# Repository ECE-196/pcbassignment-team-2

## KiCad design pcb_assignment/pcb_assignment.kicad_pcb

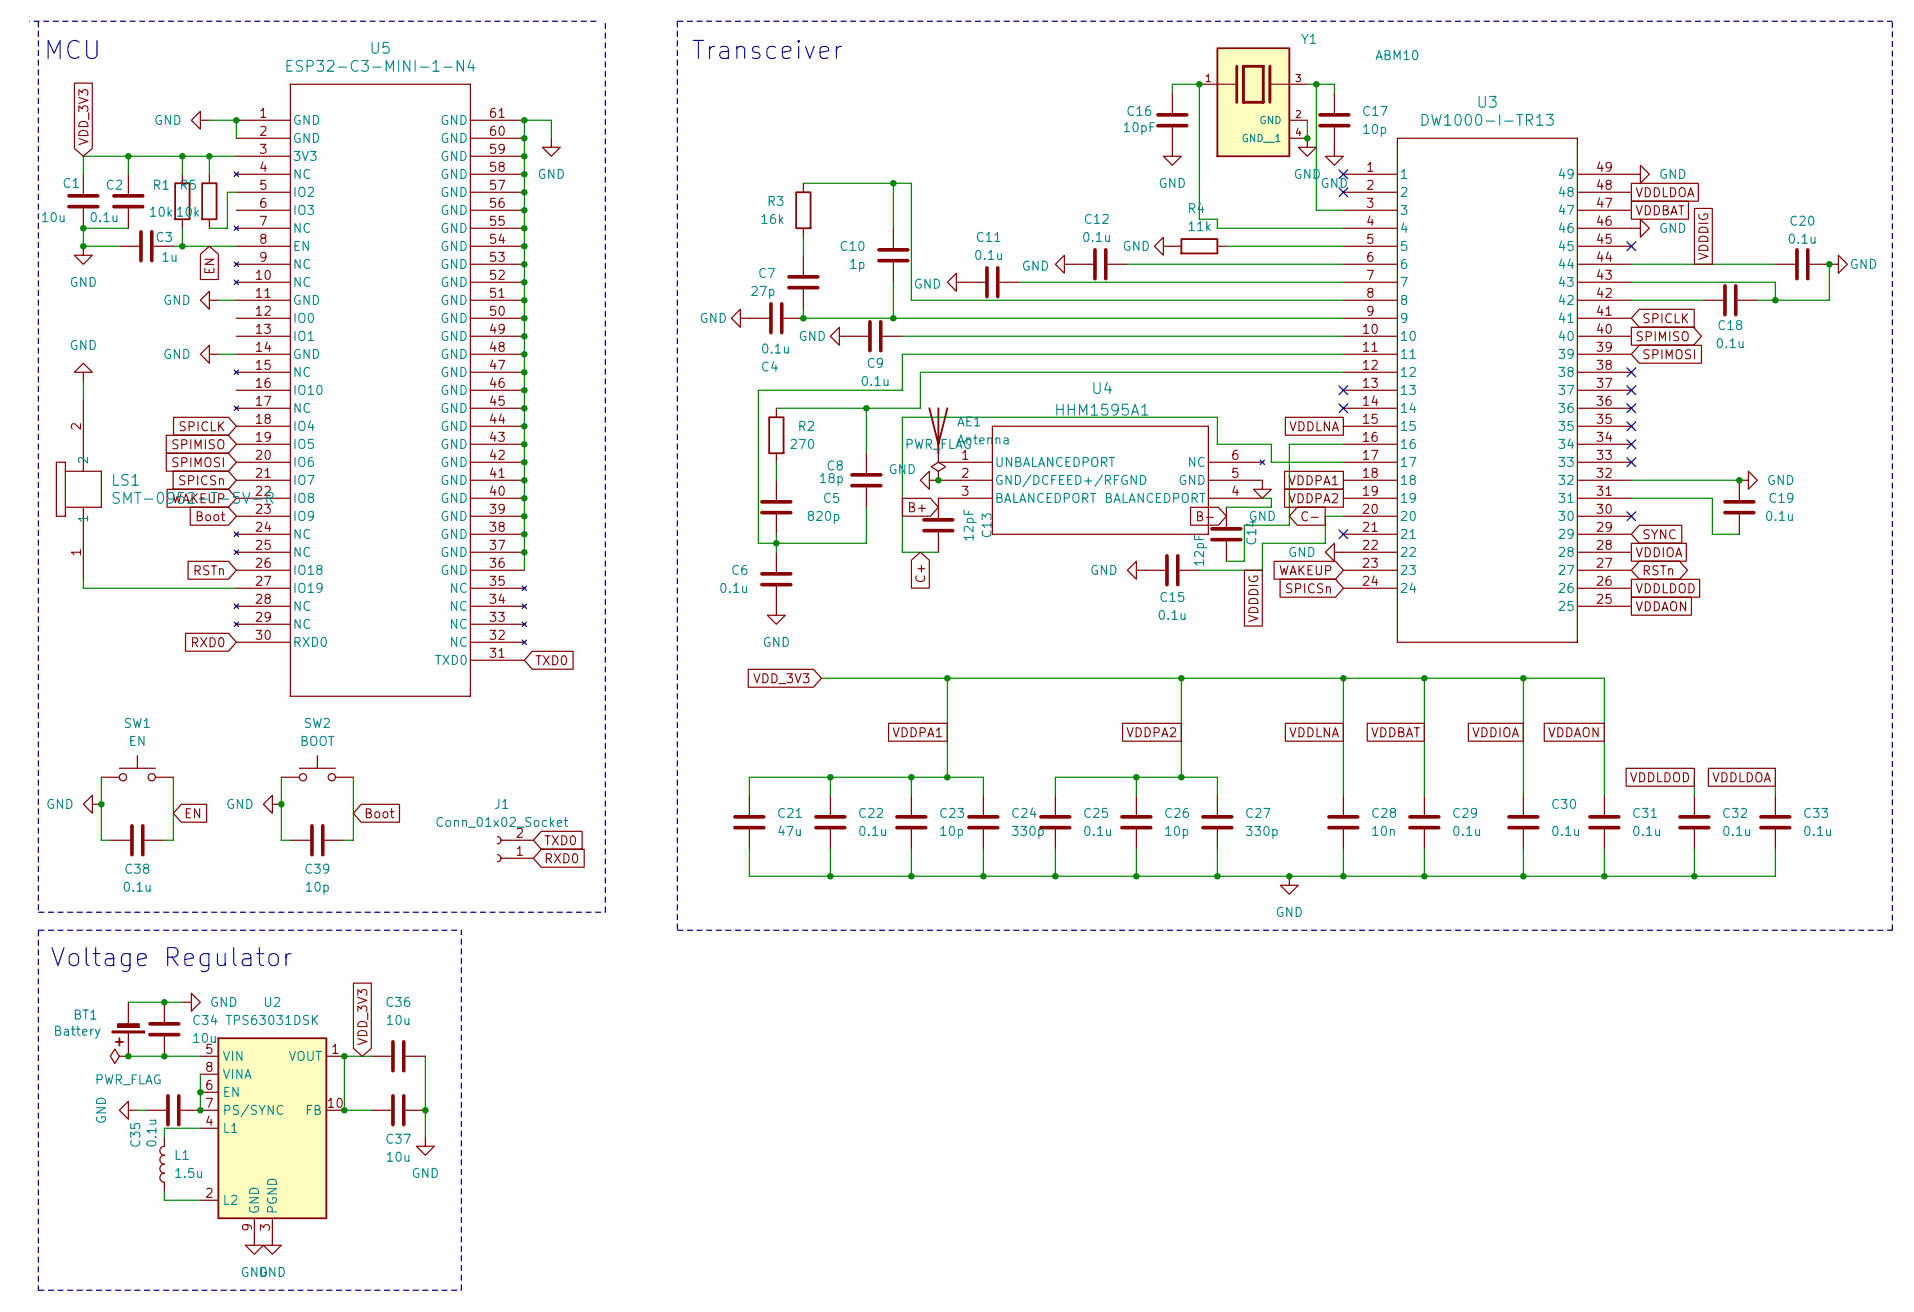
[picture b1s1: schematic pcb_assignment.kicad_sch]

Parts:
AE1: Antenna; AH086M_TAY
BT1: Battery; JST_ACH_BM02B-ACHSS-GAN-ETF_1x02-1MP_P1.20mm_Vertical
C1, C34, C36, C37: 10u; C_0402_1005Metric
C2, C4, C6, C9, C11, C12, C15, C18, C19, C20, C22, C25, C29, C30, C31, C32, C33, C35, C38: 0.1u; C_0402_1005Metric
C3: 1u; C_0402_1005Metric
C5: 820p; C_0402_1005Metric
C7: 27p; C_0402_1005Metric
C8: 18p; C_0402_1005Metric
C10: 1p; C_0402_1005Metric
C13, C14: 12pF; C_0402_1005Metric
C16: 10pF; C_0402_1005Metric
C17, C23, C26, C39: 10p; C_0402_1005Metric
C21: 47u; C_0402_1005Metric
C24, C27: 330p; C_0402_1005Metric
C28: 10n; C_0402_1005Metric
J1: Conn_01x02_Socket; PinHeader_1x02_P2.00mm_Horizontal
L1: 1.5u; L_Taiyo-Yuden_NR-30xx
LS1: SMT-0952-T-5V-R; SMT-0952-T-5V-R_PUI
R1, R5: 10k; R_0402_1005Metric
R2: 270; R_0402_1005Metric
R3: 16k; R_0402_1005Metric
R4: 11k; R_0402_1005Metric
SW1: EN; SW_PUSH_6mm
SW2: BOOT; SW_PUSH_6mm
U2: TPS63031DSK; WSON-10-1EP_2.5x2.5mm_P0.5mm_EP1.2x2mm
U3: DW1000-I-TR13; VFQFN48_12X12_QOR
U4: HHM1595A1; HHM-6_2P0X1P25
U5: ESP32-C3-MINI-1-N4; ESP32-C3-MINI-1_EXP
Y1: ABM10; XTAL_ABM10-165-38.400MHZ-T3; PARTREV 09.21.15

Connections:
Boot: C39.2, SW2.2, U5.23 (IO9)
C+: C13.2, U3.17
C-: C14.2, U3.16
EN: C3.2, C38.2, R1.2, SW1.2, U5.8 (EN)
GND: BT1.2 (-), C1.2, C2.2, C3.1, C4.2, C6.2, C9.2, C11.2, C12.2, C15.1, C16.2, C17.2, C18.2, C19.1, C20.2, C21.2, C22.2, C23.2, C24.2, C25.2, C26.2, C27.2, C28.2, C29.2, C30.2, C31.2, C32.2, C33.2, C34.1, C35.2, C36.2, C37.2, C38.1, C39.1, LS1.2, R4.2, SW1.1, SW2.1, U2.3 (PGND), U2.9 (GND), U2.11 (PGND), U3.22, U3.32, U3.43, U3.46, U3.49, U4.2 (GND/DCFEED+/RFGND), U4.5 (GND), U5.1 (GND), U5.2 (GND), U5.11 (GND), U5.14 (GND), U5.36 (GND), U5.37 (GND), U5.38 (GND), U5.39 (GND), U5.40 (GND), U5.41 (GND), U5.42 (GND), U5.43 (GND), U5.44 (GND), U5.45 (GND), U5.46 (GND), U5.47 (GND), U5.48 (GND), U5.49 (GND), U5.50 (GND), U5.51 (GND), U5.52 (GND), U5.53 (GND), U5.54 (GND), U5.55 (GND), U5.56 (GND), U5.57 (GND), U5.58 (GND), U5.59 (GND), U5.60 (GND), U5.61 (GND), Y1.2 (GND), Y1.4 (GND__1)
unnamed: AE1.1 (A), U4.1 (UNBALANCEDPORT)
unnamed: BT1.1 (+), C34.2, U2.5 (VIN)
unnamed: C5.1, R2.2
unnamed: C5.2, C6.1, C8.2, U3.11
unnamed: C7.1, R3.2
unnamed: C8.1, R2.1, U3.12
unnamed: C9.1, U3.10
unnamed: C10.1, R3.1, U3.8
unnamed: C4.1, C7.2, C10.2, U3.9
unnamed: C11.1, U3.7
unnamed: C12.1, U3.6
unnamed: C13.1, U4.3 (BALANCEDPORT)
unnamed: C14.1, U4.4 (BALANCEDPORT)
unnamed: C16.1, U3.4, Y1.1
unnamed: C17.1, U3.3, Y1.3
unnamed: C18.1, U3.42
unnamed: C19.2, U3.31
unnamed: R4.1, U3.5
unnamed: C35.1, U2.6 (EN), U2.7 (PS/SYNC), U2.8 (VINA)
unnamed: L1.2, U2.4 (L1)
unnamed: L1.1, U2.2 (L2)
unnamed: R5.2, U5.5 (IO2)
unnamed: LS1.1, U5.27 (IO19)
RSTn: U3.27, U5.26 (IO18)
RXD0: J1.1, U5.30 (RXD0)
SPICLK: U3.41, U5.18 (IO4)
SPICSn: U3.24, U5.21 (IO7)
SPIMISO: U3.40, U5.19 (IO5)
SPIMOSI: U3.39, U5.20 (IO6)
SYNC: U3.29
TXD0: J1.2, U5.31 (TXD0)
VDDAON: C1.1, C2.1, C21.1, C22.1, C23.1, C24.1, C25.1, C26.1, C27.1, C28.1, C29.1, C30.1, C31.1, C36.1, C37.1, R1.1, R5.1, U2.1 (VOUT), U2.10 (FB), U3.15, U3.18, U3.19, U3.25, U3.28, U3.47, U5.3 (3V3)
VDDDIG: C15.2, C20.1, U3.20, U3.44
VDDLDOA: C33.1, U3.48
VDDLDOD: C32.1, U3.26
WAKEUP: U3.23, U5.22 (IO8)

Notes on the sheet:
Voltage Regulator
MCU
Transceiver

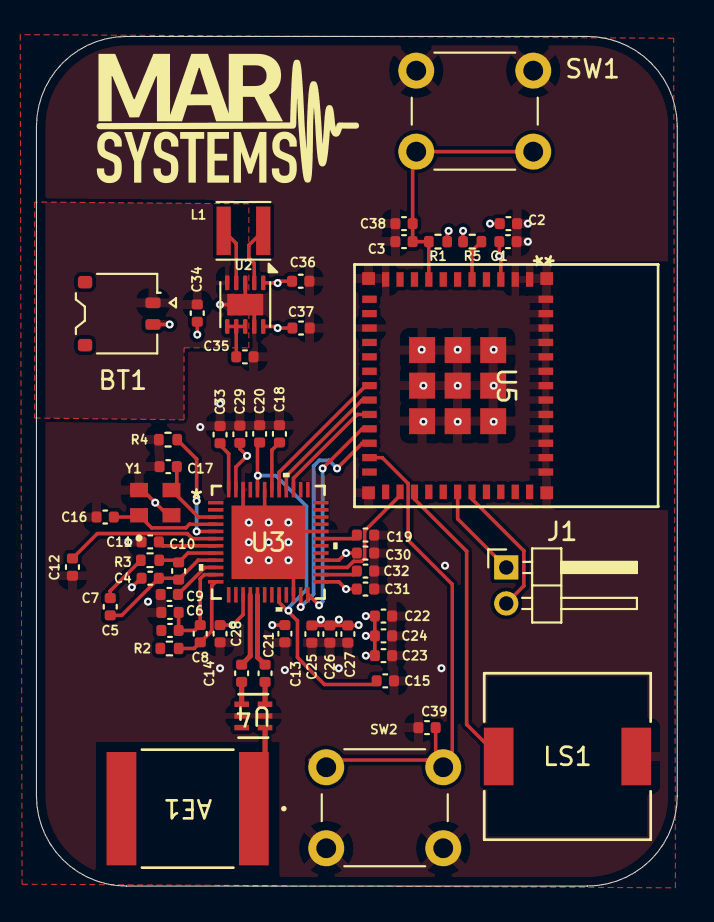
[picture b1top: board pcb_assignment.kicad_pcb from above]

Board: 2 copper layers, 35.6 x 47.2 mm, 56 parts (0 on the bottom side), 40 nets.

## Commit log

2024-04-28 add deadline
2024-04-28 Added transceiver schematic inside pcb assignment folder
2024-05-04 Finished schematic and pcb design, added gerber files, edited changelog
